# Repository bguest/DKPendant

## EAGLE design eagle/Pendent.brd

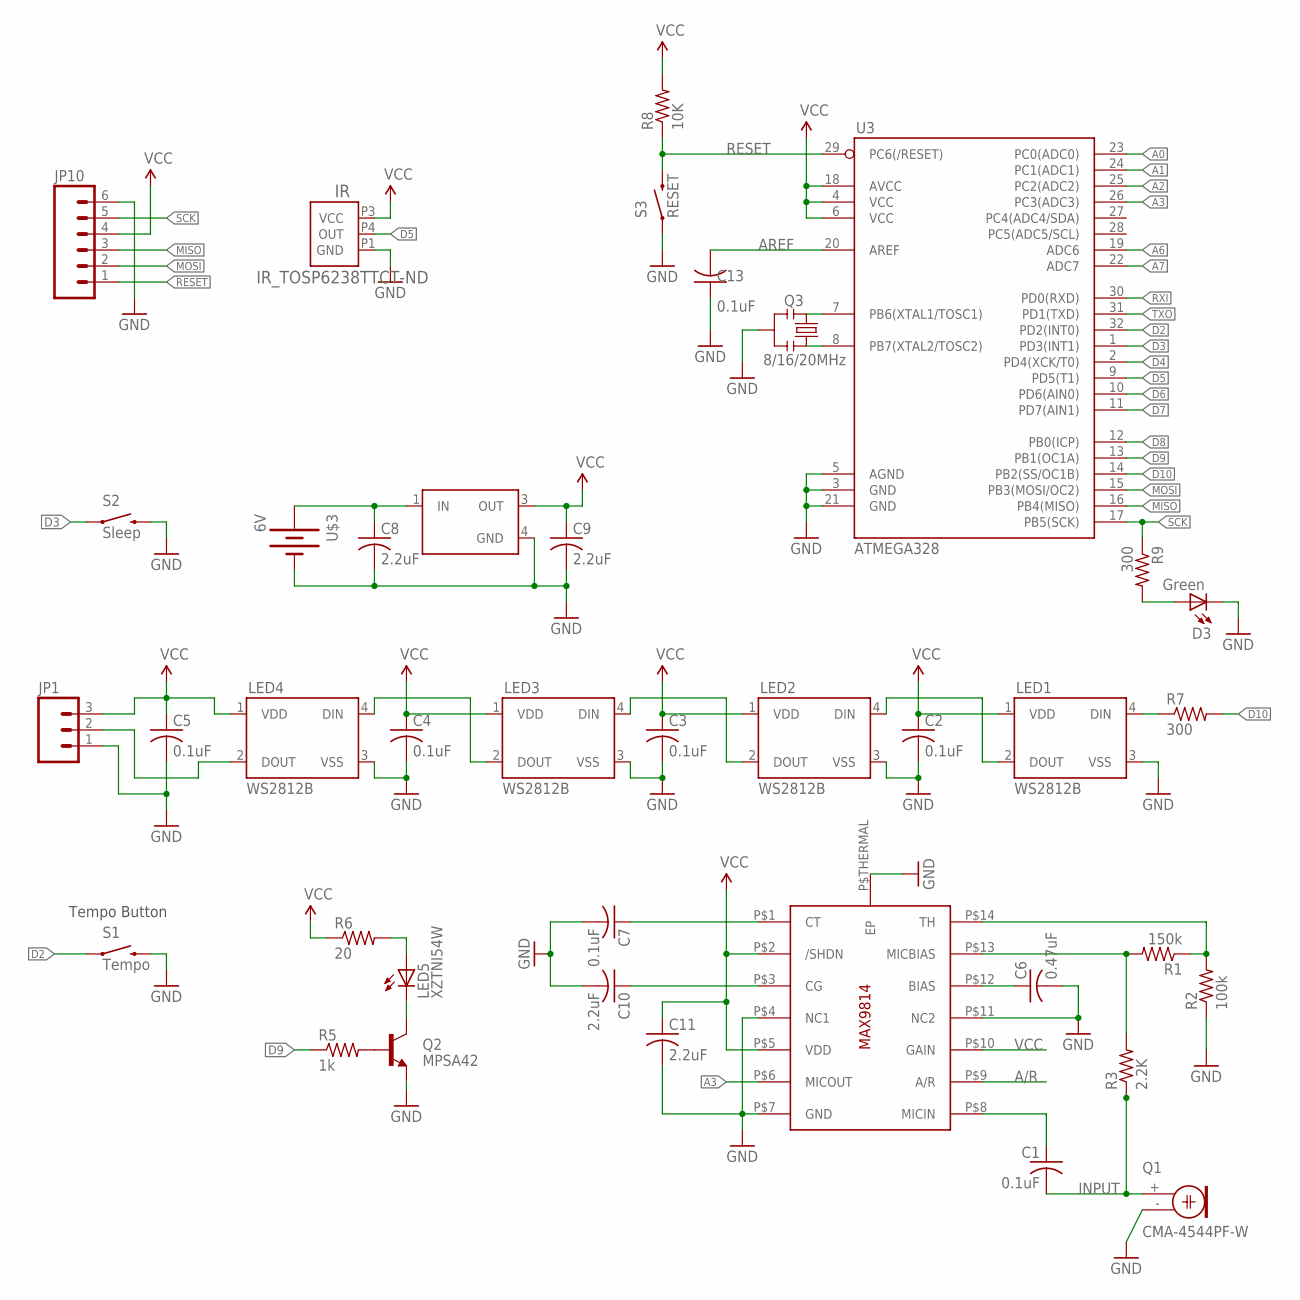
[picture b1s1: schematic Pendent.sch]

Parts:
C1, C2, C3, C4, C5, C7, C13: 0.1uF; C0805K
C6: 0.47uF; C0805K
C8, C9, C10, C11: 2.2uF; C0805K
D3: Green; CHIPLED_0805
IR: IR_TOSP6238TTCT-ND; TOSP62XX_A
JP1: M03PTH; 1X03
JP10: M06SIP; 1X06
LED1, LED2, LED3, LED4: WS2812B
LED5: XZTNI54W; LED5MM
Q1: CMA-4544PF-W; 9.7ELECTRET
Q2: MPSA42; SOT23-3
Q3: 8/16/20MHz; RESONATOR-SMD-1:1
R1: 150k; R0805
R2: 100k; R0805
R3: 2.2K; R0805
R5: 1k; R0805
R6: 20; R0805
R7, R9: 300; R0805
R8: 10K; R0805
S1: Tempo; 2-1437565-7
S2: Sleep; TACTILE-SWITCH-SMD
S3: RESET; TACTILE-SWITCH-SMD-ALT01
U1: MAX9814TDFN14; TDFN14_3X3MM
U2: LF50ABDT-TR; DPAK
U3: ATMEGA328; TQFP32-08
U$3: 6V; BH2X-2032-SM

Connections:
A0: U3.23 (PC0(ADC0))
A1: U3.24 (PC1(ADC1))
A2: U3.25 (PC2(ADC2))
A3: U1.P$6 (MICOUT), U3.26 (PC3(ADC3))
A6: U3.19 (ADC6)
A7: U3.22 (ADC7)
A/R: U1.P$9 (A/R)
AREF: C13.2, U3.20 (AREF)
D2: S1.P1 (1), S1.P2 (1), U3.32 (PD2(INT0))
D3: S2.1, S2.2 (1), U3.1 (PD3(INT1))
D4: U3.2 (PD4(XCK/T0))
D5: IR.P4 (OUT), U3.9 (PD5(T1))
D6: U3.10 (PD6(AIN0))
D7: U3.11 (PD7(AIN1))
D8: U3.12 (PB0(ICP))
D9: R5.1, U3.13 (PB1(OC1A))
D10: R7.2, U3.14 (PB2(SS/OC1B))
GND: C2.2, C3.2, C4.2, C5.2, C6.2, C7.2, C8.2, C9.2, C10.2, C11.2, C13.1, D3.C, IR.P1 (GND), JP1.1, JP10.6, LED1.3 (VSS), LED2.3 (VSS), LED3.3 (VSS), LED4.3 (VSS), Q1.- (1), Q2.2 (E), Q3.2, R2.1, S1.P3 (2), S1.P4 (2), S2.3 (2), S2.4 (2), S3.1, S3.2 (1), U1.P$4 (NC1), U1.P$7 (GND), U1.P$11 (NC2), U1.P$THERMAL (EP), U2.4 (GND), U3.3 (GND), U3.5 (AGND), U3.21 (GND), U$3.GND (-)
INPUT: C1.2, Q1.+ (2), R3.1
MISO: JP10.3, U3.16 (PB4(MISO))
MOSI: JP10.2, U3.15 (PB3(MOSI/OC2))
unnamed: D3.A, R9.2
unnamed: LED2.2 (DOUT), LED3.4 (DIN)
unnamed: LED3.2 (DOUT), LED4.4 (DIN)
unnamed: C1.1, U1.P$8 (MICIN)
unnamed: JP1.2, LED4.2 (DOUT)
unnamed: C6.1, U1.P$12 (BIAS)
unnamed: C7.1, U1.P$1 (CT)
unnamed: C10.1, U1.P$3 (CG)
unnamed: R1.1, R2.2, U1.P$14 (TH)
unnamed: R1.2, R3.2, U1.P$13 (MICBIAS)
unnamed: Q3.3, U3.8 (PB7(XTAL2/TOSC2))
unnamed: Q2.1 (B), R5.2
unnamed: LED5.K (C), Q2.3 (C)
unnamed: LED5.A, R6.2
unnamed: Q3.1, U3.7 (PB6(XTAL1/TOSC1))
unnamed: LED1.4 (DIN), R7.1
unnamed: LED1.2 (DOUT), LED2.4 (DIN)
RESET: JP10.1, R8.1, S3.3 (2), S3.4 (2), U3.29 (PC6(/RESET))
RXI: U3.30 (PD0(RXD))
SCK: JP10.5, R9.1, U3.17 (PB5(SCK))
TXO: U3.31 (PD1(TXD))
VCC: C2.1, C3.1, C4.1, C5.1, C9.1, C11.1, IR.P3 (VCC), JP1.3, JP10.4, LED1.1 (VDD), LED2.1 (VDD), LED3.1 (VDD), LED4.1 (VDD), R6.1, R8.2, U1.P$2 (/SHDN), U1.P$5 (VDD), U1.P$10 (GAIN), U2.3 (OUT), U3.4 (VCC), U3.6 (VCC), U3.18 (AVCC)
VIN: C8.1, U2.1 (IN), U$3.P$1 (+), U$3.P$2 (+)

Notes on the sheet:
Tempo Button

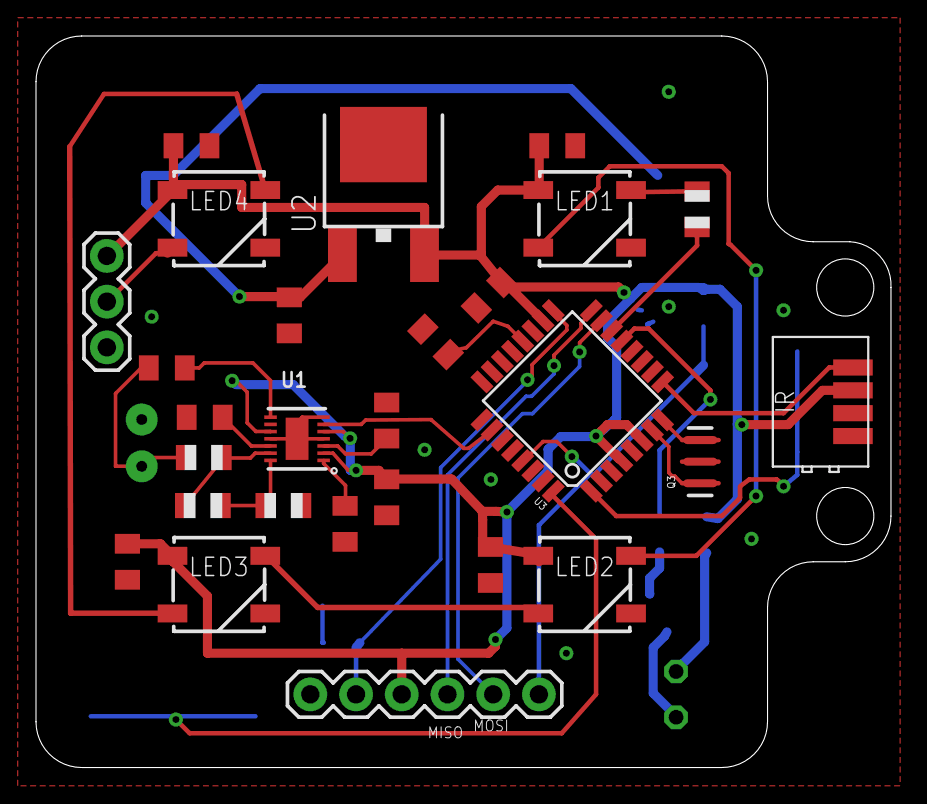
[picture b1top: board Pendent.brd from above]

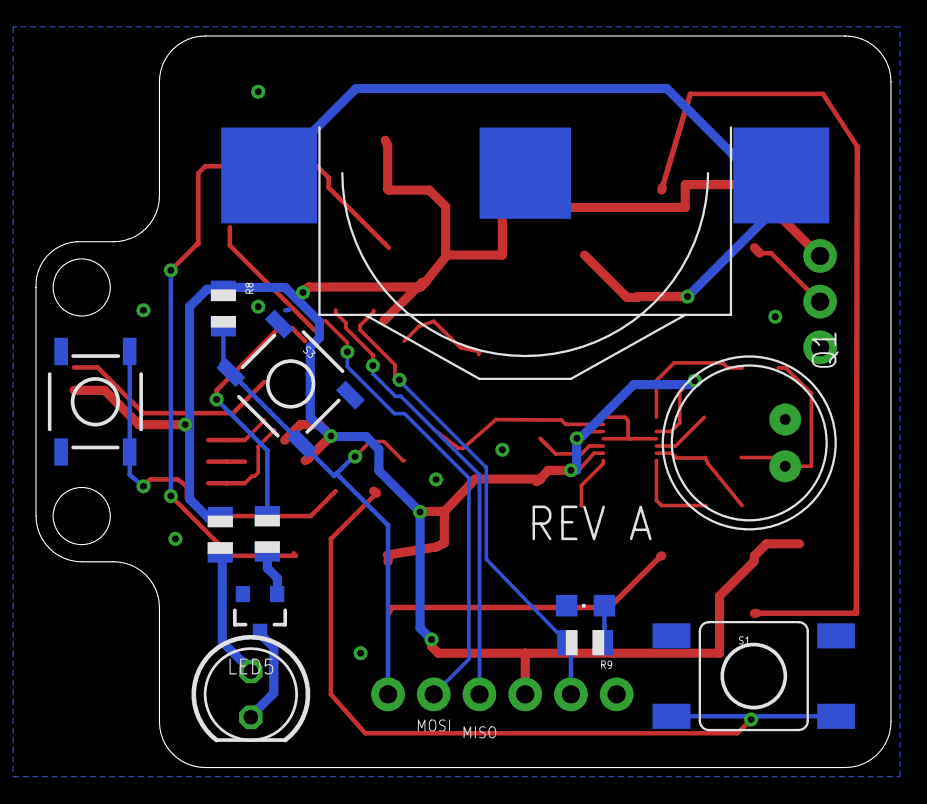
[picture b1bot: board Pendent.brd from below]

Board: 2 copper layers, 47.5 x 40.6 mm, 39 parts (12 on the bottom side), 32 nets.

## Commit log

2015-10-08 second first commit
2015-10-08 Add Double Tap, Add FastLED
2015-10-12 Got spin effect working.
2015-10-12 Add fix_fft
2015-10-13 Add Sound effects
2015-10-13 Add Levels Effect
2015-10-15 compatable with ATTiny85
2015-10-15 Switch to using AdaFruit_NeoPixel
2015-10-25 Removed Leds and Pixels Classes
2015-10-25 Fix temo held on.
2015-10-25 Board Layout
2015-10-25 Add IRSend add IR LED to schematic
2015-10-28 Add FadeShift
2015-10-29 Updates to shift-fade
2015-10-29 Experiment with PWM in ATmeg328
2015-10-29 stuff
2015-10-30 Modificaitons to Board to Accomidate ATmega328P-AU
2015-11-08 Updates to effects and sent data (Not ATtiny Specific)
2015-11-08 Change tempo button to external pull down (ATtiny Specfic)
2015-11-08 Add External LED Connection
2015-11-09 Switch to correct battery footprint, switch to V13 isp
2015-11-10 Add IR Receiver
2015-11-12 Add Push On Button
2015-11-12 Add Code for power button
2015-11-13 Add Stuff from ATtiny85 branch
2015-11-13 Remove non-working mosfet, switch to using power down
2015-11-14 Add Sleep functionality
2015-11-14 Wire up Sleep Button
2015-11-15 Add Bigger Tempo Button to board
2015-11-22 Shift Bands
2015-12-03 REV A
2015-12-05 Fix sleep, add IRrecive, make hues global across effects
2015-12-07 Add Snake and RandomOn, Snake needs work
2015-12-08 WIP: Snake
2015-12-15 WIP: RandomSound
2015-12-17 Modifications fo RandomSound
2015-12-20 Add RawVolume

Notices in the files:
parts and their libraries:
SparkFun-LED: Licensing: CC v3.0 Share-Alike You are welcome to use this library for commercial purposes.
SparkFun-Electromechanical: Licensing: Creative Commons ShareAlike 4.0 International - https://creativecommons.org/licenses/by-sa/4.0
